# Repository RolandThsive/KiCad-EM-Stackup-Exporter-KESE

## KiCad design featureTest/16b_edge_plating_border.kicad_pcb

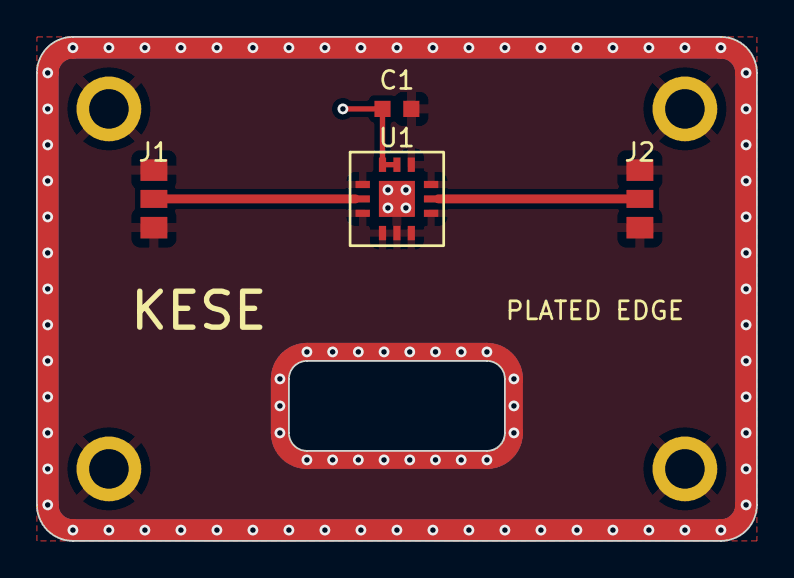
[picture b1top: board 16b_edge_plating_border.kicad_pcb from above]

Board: 4 copper layers, 40.0 x 28.0 mm, 8 parts (0 on the bottom side), 4 nets.

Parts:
C1: C0603
H1, H2, H3, H4: MountingHole
J1, J2: RFLaunch
U1: QFN12

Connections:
+3V3: C1.1, U1.7, U1.8
GND: C1.2, H1.1, H2.1, H3.1, H4.1, J1.2, J1.3, J2.2, J2.3, U1.1, U1.3, U1.4, U1.6, U1.9, U1.10, U1.11, U1.12, U1.13
RF_IN: J1.1, U1.2
RF_OUT: J2.1, U1.5
